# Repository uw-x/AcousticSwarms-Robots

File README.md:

## Hardware
The hardware design for the robots used in the acoustic swarms, including the circuits and PCB files.

## Firmware
This subfolder contains the source code for the firmware we upload on the robots. The firmware is compiled and uploaded using [Segger Embedded Studio v7.22](https://www.segger.com/downloads/embedded-studio/) and the [nRF5 SDK v17.0.1](https://www.nordicsemi.com/Products/Development-software/nRF5-SDK/Download#infotabs). 

## Receiver
This subfolder contains the source code and firmware for the receiver used to transmit data to and from the robot swarm. It also contains the 2D robot localization algorithm.

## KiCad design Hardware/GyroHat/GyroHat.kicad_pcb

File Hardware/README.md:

# Robot Hardware
This subfolder contains information pertaining to the robot design files.

## What's included
This folder contains the following directories:

**CAD**: STL files for the 3D models used. The base station is printed using an Ultimaker 3 with white PLA. The rest of the design files use a Formlabs Form 3 printer with black resin. The robot body takes inspiration from [Zooids](https://github.com/ShapeLab/SwarmUI), with various modifications. However, we use the 3D printed wheels are the same.

**Robot**: BoM & PCB design files for the robot main circuit.

**GyroHat**: BoM & PCB design files for the gyroscope hat on the top of the robot.

**SensorBars**: BoM & PCB design files for the sensor bar used to detect edges.

## How to use
To use these circuit design files, you will need the circuit design software KiCad. Simply import the schematics and PCB layouts into your preferred software and you can begin customizing and optimizing the design to fit your specific needs.

During assembly, we place two wire connecting the metallic balls at the bottom of the robot to the PCB at the top. One ball is connected to the circuit ground while the other is connected through the +5V battery input (the Vin TestPoint in the PCB). For protection, this ball is connected through a [diode](https://www.digikey.com/ordering/shoppingcart?display=yes&itemSeqs=398627123,398628073,398633233&reprice=2).
We use [micro DC motors](https://www.firgelliauto.com/products/mini-motor-micro-motor) from Firgelli Auto.
We use [M2x0.4mm Thread, 6m Long screws](https://www.mcmaster.com/catalog/129/3394/90116A010) and [1/8 inch diameter aluminium balls](https://www.mcmaster.com/catalog/129/4186/34665K29) from McMaster-Carr.
We use [M1.5x8 Buna-N O-Ring](https://www.amazon.com/gp/product/B00595LLJK/ref=ppx_yo_dt_b_asin_title_o05_s00?ie=UTF8&th=1) from Amazon.

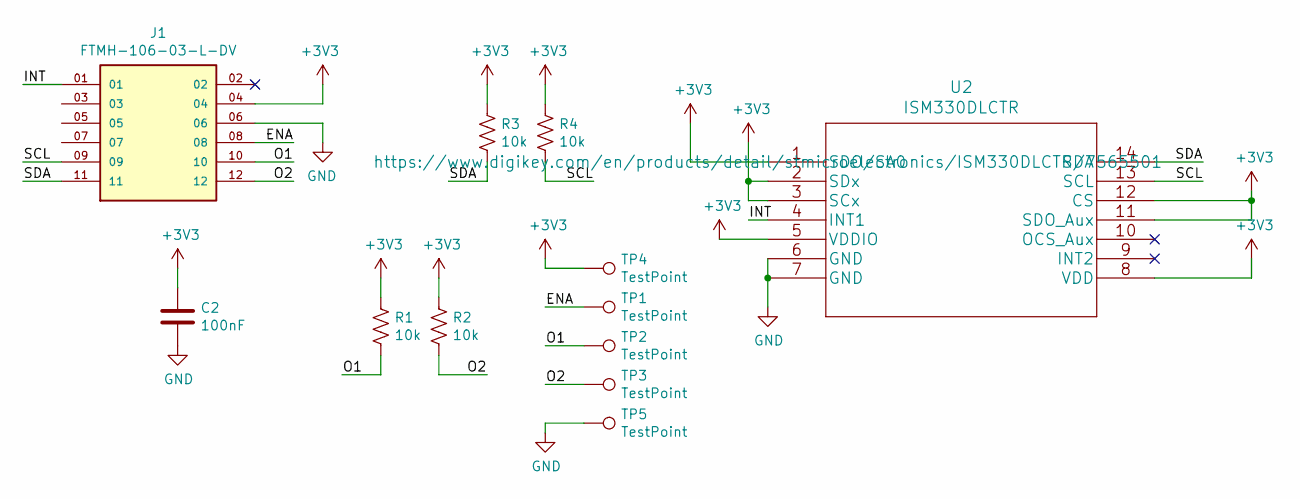
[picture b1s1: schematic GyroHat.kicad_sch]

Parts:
C2: 100nF; C_0402_1005Metric
J1: FTMH-106-03-L-DV; SAMTEC_FTMH-106-03-L-DV
R1, R2, R3, R4: 10k; R_0402_1005Metric
TP1, TP2, TP3, TP4, TP5: TestPoint; Wire Pad
U2: ISM330DLCTR; LGA-14_3x2.5mm_P0.5mm_LayoutBorder3x4y

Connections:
+3V3: C2.1, J1.04, R1.1, R2.1, R3.1, R4.1, TP4.1, U2.1 (SDO/SA0), U2.2 (SDx), U2.3 (SCx), U2.5 (VDDIO), U2.8 (VDD), U2.11 (SDO_Aux), U2.12 (CS)
/ENA: J1.08, TP1.1
/INT: J1.01, U2.4 (INT1)
/O1: J1.10, R1.2, TP2.1
/O2: J1.12, R2.2, TP3.1
/SCL: J1.09, R4.2, U2.13 (SCL)
/SDA: J1.11, R3.2, U2.14 (SDA)
GND: C2.2, J1.06, TP5.1, U2.6 (GND), U2.7 (GND)

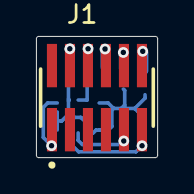
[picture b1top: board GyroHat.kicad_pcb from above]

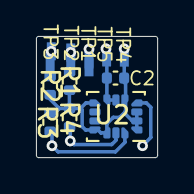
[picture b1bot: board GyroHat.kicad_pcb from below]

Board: 2 copper layers, 6.7 x 6.7 mm, 12 parts (11 on the bottom side), 8 nets.

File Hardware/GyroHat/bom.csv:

Component,Description,References,Value,Footprint,Quantity Per PCB,Datasheet,MANUFACTURER
1,CAP CER 0.1UF 25V X5R 0402,C2,100nF,C_0402_1005Metric,1,https://media.digikey.com/pdf/Data%20Sheets/Samsung%20PDFs/C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,Samsung Electro-Mechanics
2,CONN HEADER SMD 12POS 1MM,J1,FTMH-106-03-L-DV,SAMTEC_FTMH-106-03-L-DV,1,https://www.digikey.com/en/products/detail/samtec-inc/FTMH-1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,SAMTEC
3,RES SMD 10K OHM 5% 1/5W 0402,R1 R2 R3 R4,10k,R_0402_1005Metric,4,https://fscdn.rohm.com/en/products/databook/datasheet/passiv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,Rohm Semiconductor
4,INEMO INERTIAL MODULE,U2,ISM330DLCTR,LGA-14_3x2.5mm_P0.5mm_LayoutBorder3x4y,1,https://www.digikey.com/en/products/detail/stmicroelectronic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,STMicroelectronics
,,,,,,,
,,,,,,,
,,,,,,,
,,,,,,,
,,,,,,,
Component Groups:,4,,,,,,
Component Count:,7,,,,,,
Fitted Components:,7,,,,,,
Number of PCBs:,1,,,,,,
Total components:,7,,,,,,
Schematic Version:,,,,,,,
Schematic Date:,,,,,,,
PCB Variant:,default,,,,,,
BoM Date:,Fri 04 Aug 2023 09:19:59 AM,,,,,,
Schematic Source:,GyroHat.kicad_sch,,,,,,
KiCad Version:,Eeschema 6.0.2+dfsg-1,,,,,,

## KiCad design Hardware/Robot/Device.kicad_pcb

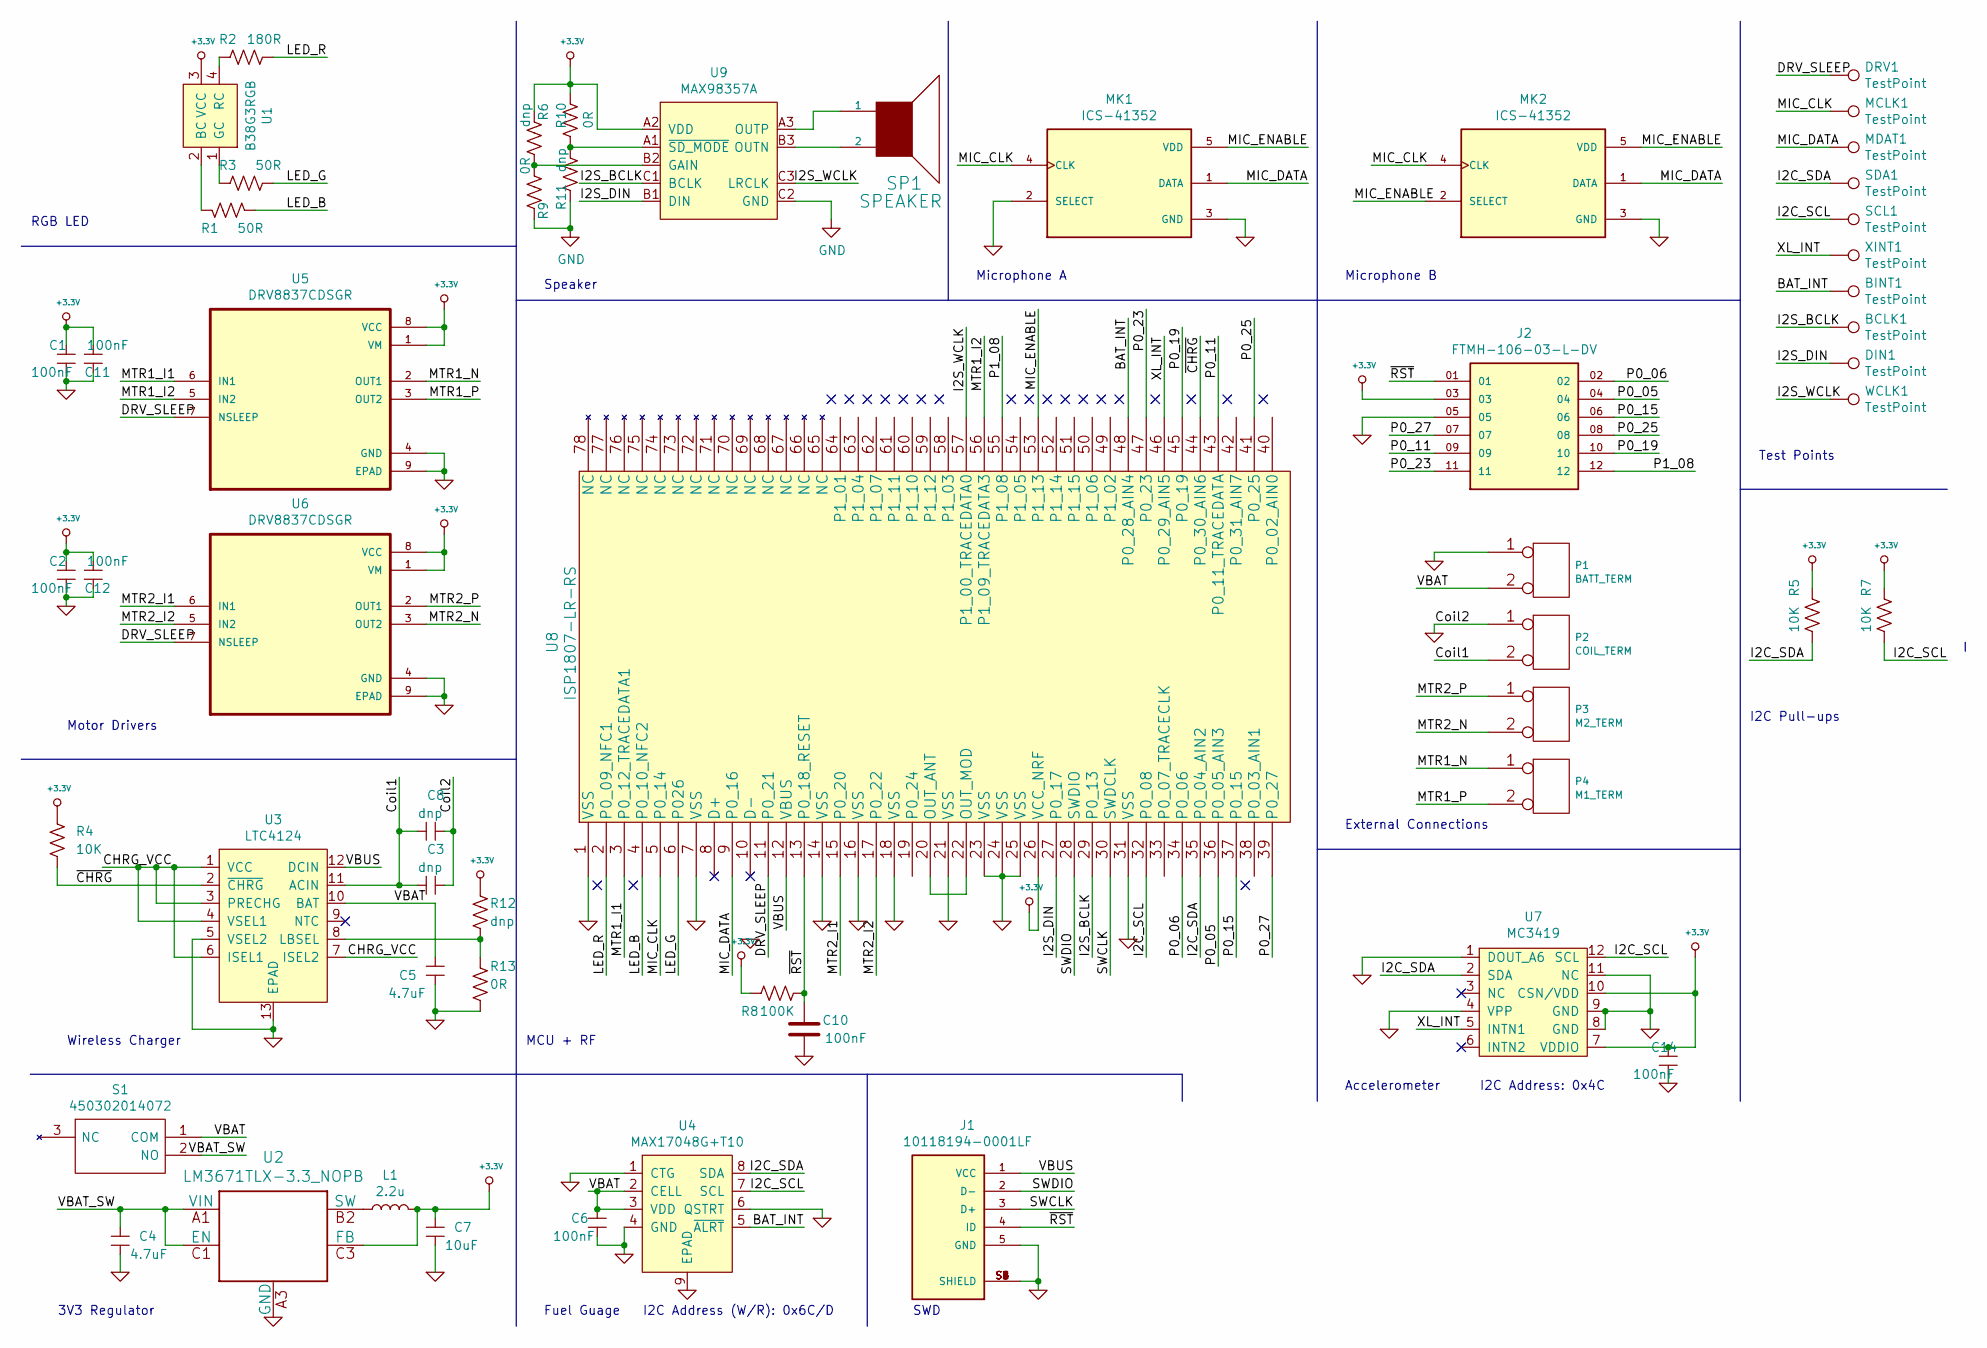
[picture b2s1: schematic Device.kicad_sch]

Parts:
BCLK1: TestPoint; TestPoint_Pad_D1.0mm
BINT1: TestPoint; TestPoint_Pad_D1.0mm
C1, C2, C6, C10, C11, C12, C14: 100nF; C_0402_1005Metric; Manufacturer P/N CL05A104KA5NNNC
C3, C8: dnp; C_0402_1005Metric
C4, C5: 4.7uF; C_0603_1608Metric; Manufacturer P/N CL10A475KQ8NNNC
C7: 10uF; C_0603_1608Metric; Manufacturer P/N 0603YW106MAT2A
DIN1: TestPoint; TestPoint_Pad_D1.0mm
DRV1: TestPoint; TestPoint_Pad_D1.0mm
J1: 10118194-0001LF; AMPHENOL_10118194-0001LF; PARTREV B
J2: FTMH-106-03-L-DV; SAMTEC_FTMH-106-03-L-DV; Manufacturer P/N FTMH-106-03-L-DV
L1: 2.2u; L_0805_2012Metric; Manufacturer P/N DFE201210U-2R2M=P2
MCLK1: TestPoint; TestPoint_Pad_D1.0mm
MDAT1: TestPoint; TestPoint_Pad_D1.0mm
MK1, MK2: ICS-41352; MIC_ICS-41350; Manufacturer P/N ICS-41352
P1: BATT_TERM; JST_ACH_BM02B-ACHSS-GAN-ETF_1x02-1MP_P1.20mm_Vertical; Manufacturer P/N BM02B-ACHSS-GAN-ETF(LF)(SN
P2: COIL_TERM; TestPoint_2Pads_Pitch2.54mm_Drill0.8mm
P3: M2_TERM; PinHeader_1x02_P1.27mm_Vertical
P4: M1_TERM; PinHeader_1x02_P1.27mm_Vertical
R1, R3: 50R; R_0402_1005Metric; Manufacturer P/N AC0402JR-0750RL
R2: 180R; R_0402_1005Metric; Manufacturer P/N CRGCQ0402F180K
R4, R5, R7: 10K; R_0402_1005Metric; Manufacturer P/N ESR01MZPJ103
R6, R11, R12: dnp; R_0402_1005Metric
R8: 100K; R_0402_1005Metric; Manufacturer P/N RT0402BRE07100KL
R9, R10, R13: 0R; R_0402_1005Metric; Manufacturer P/N RMCF0402ZT0R00
S1: 450302014072; Manufacturer P/N 450302014072
SCL1: TestPoint; TestPoint_Pad_D1.0mm
SDA1: TestPoint; TestPoint_Pad_D1.0mm
SP1: SPEAKER; CUI_CMT-4023S-SMT-TR; Manufacturer P/N SMT-0440-T-HT-R
U1: B38G3RGB; B38G3RGB10D0003H2U1930; Manufacturer P/N B38G3RGB-10D0003H2U1930
U2: LM3671TLX-3.3_NOPB; LM3671TLX-3.3&slash_NOPB; Manufacturer P/N LM3671TLX-3.3/NOPB
U3: LTC4124; LTC4124EV-TRMPBF; Manufacturer P/N LTC4124EV#TRMPBF
U4: MAX17048G+T10; SON50P200X200X80-9N; Manufacturer P/N MAX17048G+T10
U5, U6: DRV8837CDSGR; SON50P200X200X80-9N; Manufacturer P/N DRV8837CDSGR
U7: MC3419; LGA-12_2x2mm_P0.5mm; Manufacturer P/N MC3419
U8: ISP1807-LR-RS; Manufacturer P/N ISP1807-LR-RS
U9: MAX98357A; Maxim_WLP-9_1.595x1.415_Layout3x3_P0.4mm_Ball0.27mm_Pad0.25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; Manufacturer P/N MAX98357AEWL+T
WCLK1: TestPoint; TestPoint_Pad_D1.0mm
XINT1: TestPoint; TestPoint_Pad_D1.0mm

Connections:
+3.3V: C1.1, C2.1, C7.2, C11.2, C12.2, C14.1, J2.03, L1.2, R4.1, R5.1, R6.2, R7.1, R8.1, R10.1, R12.1, U1.3 (VCC), U2.C3 (FB), U5.1 (VM), U5.8 (VCC), U6.1 (VM), U6.8 (VCC), U7.7 (VDDIO), U7.10 (CSN/VDD), U8.26 (VCC_NRF), U9.A2 (VDD)
/BAT_INT: BINT1.1, U4.5 (~ALRT), U8.48 (P0_28_AIN4)
/CHRG_VCC: U3.1 (VCC), U3.3 (PRECHG), U3.4 (VSEL1), U3.6 (ISEL1), U3.7 (ISEL2)
/Coil1: C3.2, C8.2, P2.2 (PM), U3.11 (ACIN)
/DRV_SLEEP: DRV1.1, U5.7 (NSLEEP), U6.7 (NSLEEP), U8.11 (P0_21)
/I2C_SCL: R7.2, SCL1.1, U4.7 (SCL), U7.12 (SCL), U8.32 (P0_08)
/I2C_SDA: R5.2, SDA1.1, U4.8 (SDA), U7.2 (SDA), U8.35 (P0_04_AIN2)
/I2S_BCLK: BCLK1.1, U8.29 (P0_13), U9.C1 (BCLK)
/I2S_DIN: DIN1.1, U8.27 (P0_17), U9.B1 (DIN)
/I2S_WCLK: U8.57 (P1_00_TRACEDATA0), U9.C3 (LRCLK), WCLK1.1
/LED_B: R1.2, U8.4 (P0_10_NFC2)
/LED_G: R3.2, U8.6 (P026)
/LED_R: R2.2, U8.2 (P0_09_NFC1)
/MIC_CLK: MCLK1.1, MK1.4 (CLK), MK2.4 (CLK), U8.5 (P0_14)
/MIC_DATA: MDAT1.1, MK1.1 (DATA), MK2.1 (DATA), U8.9 (P0_16)
/MIC_ENABLE: MK1.5 (VDD), MK2.2 (SELECT), MK2.5 (VDD), U8.53 (P1_13)
/MTR1_I1: U5.6 (IN1), U8.3 (P0_12_TRACEDATA1)
/MTR1_I2: U5.5 (IN2), U8.56 (P1_09_TRACEDATA3)
/MTR1_N: P4.1, U5.2 (OUT1)
/MTR1_P: P4.2 (PM), U5.3 (OUT2)
/MTR2_I1: U6.6 (IN1), U8.15 (P0_20)
/MTR2_I2: U6.5 (IN2), U8.17 (P0_22)
/MTR2_N: P3.2 (PM), U6.3 (OUT2)
/MTR2_P: P3.1, U6.2 (OUT1)
/P0_05: J2.04, U8.36 (P0_05_AIN3)
/P0_06: J2.02, U8.34 (P0_06)
/P0_11: J2.09, U8.43 (P0_11_TRACEDATA)
/P0_15: J2.06, U8.37 (P0_15)
/P0_19: J2.10, U8.45 (P0_19)
/P0_23: J2.11, U8.47 (P0_23)
/P0_25: J2.08, U8.41 (P0_25)
/P0_27: J2.07, U8.39 (P0_27)
/P1_08: J2.12, U8.55 (P1_08)
/SWCLK: J1.3 (D+), U8.30 (SWDCLK)
/SWDIO: J1.2 (D-), U8.28 (SWDIO)
/VBAT: C5.1, C6.2, P1.2 (PM), S1.1 (COM), U3.10 (BAT), U4.2 (CELL), U4.3 (VDD)
/VBAT_SW: C4.2, S1.2 (NO), U2.A1 (VIN), U2.C1 (EN)
/VBUS: J1.1 (VCC), U3.12 (DCIN), U8.12 (VBUS)
/XL_INT: U7.5 (INTN1), U8.46 (P0_29_AIN5), XINT1.1
/~CHRG: R4.2, U3.2 (~CHRG), U8.44 (P0_30_AIN6)
/~RST: C10.1, J1.4 (ID), J2.01, R8.2, U8.13 (P0_18_RESET)
GND: C1.2, C2.2, C3.1, C4.1, C5.2, C6.1, C7.1, C8.1, C10.2, C11.1, C12.1, C14.2, J1.5 (GND), J1.S1 (SHIELD), J1.S2 (SHIELD), J1.S3 (SHIELD), J1.S4 (SHIELD), J1.S5 (SHIELD), J1.S6 (SHIELD), J2.05, MK1.2 (SELECT), MK1.3 (GND), MK2.3 (GND), P1.1, P2.1, R9.1, R11.1, R13.2, U2.A3 (GND), U3.5 (VSEL2), U3.13 (EPAD), U4.1 (CTG), U4.4 (GND), U4.6 (QSTRT), U4.9 (EPAD), U5.4 (GND), U5.9 (EPAD), U6.4 (GND), U6.9 (EPAD), U7.1 (DOUT_A6), U7.4 (VPP), U7.8 (GND), U7.9 (GND), U7.11 (NC), U8.1 (VSS), U8.7 (VSS), U8.14 (VSS), U8.16 (VSS), U8.18 (VSS), U8.21 (VSS), U8.23 (VSS), U8.24 (VSS), U8.25 (VSS), U8.31 (VSS), U9.C2 (GND)
unnamed: L1.1, U2.B2 (SW)
unnamed: R1.1, U1.2 (BC)
unnamed: R2.1, U1.4 (RC)
unnamed: R3.1, U1.1 (GC)
unnamed: R6.1, R9.2, U9.B2 (GAIN)
unnamed: R10.2, R11.2, U9.A1 (~SD_MODE)
unnamed: R12.2, R13.1, U3.8 (LBSEL)
unnamed: SP1.1, U9.A3 (OUTP)
unnamed: SP1.2, U9.B3 (OUTN)
unnamed: U8.20 (OUT_ANT), U8.22 (OUT_MOD)

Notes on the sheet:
3V3 Regulator
I2C Pull-ups
Test Points
Wireless Charger
SWD
MCU + RF
RGB LED
Motor Drivers
Speaker
Fuel Guage
Microphone B
External Connections
Accelerometer
Microphone A
I2C Address: 0x4C
I2C Address (W/R): 0x6C/D

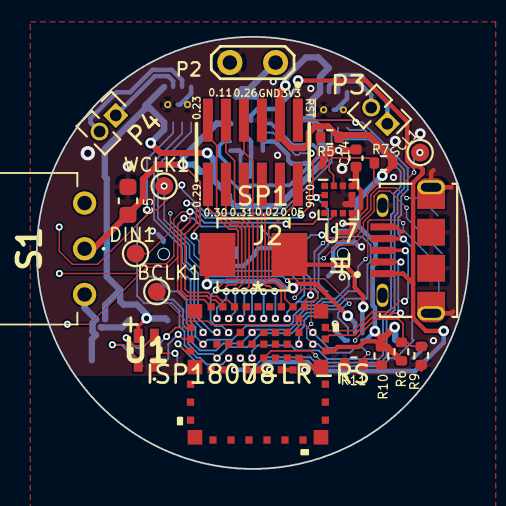
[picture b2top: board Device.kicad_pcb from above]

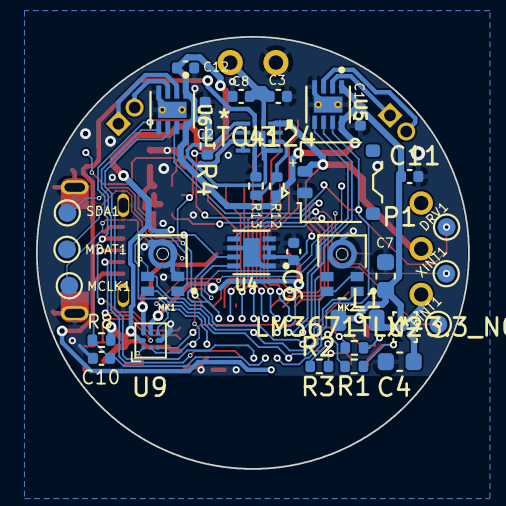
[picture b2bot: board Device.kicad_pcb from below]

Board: 2 copper layers, 24.0 x 24.0 mm, 55 parts (33 on the bottom side), 52 nets.

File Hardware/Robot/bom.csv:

#,References,Value,Datasheet,Description,Manufacturer,Manufacturer P/N,Vendor,Vendor P/N,Quantity,Notes
1,">  C3, C8",dnp,,Do Not Place,,,,,2,
2,">  C4, C5",4.7uF,https://media.digikey.com/pdf/Data%20Sheets/Samsung%20PDFs/C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,CAP CER 4.7UF 10V X5R 0603,Samsung Electro-Mechanics,CL10A475KQ8NNNC,Digi-key,1276-1045-2-ND,2,
3,    C7,10uF,https://datasheets.kyocera-avx.com/x6s-dielectric.pdf,CAP CER 10UF 16V X6S 0603,KYOCERA AVX,0603YW106MAT2A,Digi-key,478-0603YW106MAT2ATR-ND,1,
4,">  C1, C2, C6, C10-C12, C14",100nF,https://media.digikey.com/pdf/Data%20Sheets/Samsung%20PDFs/C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,CAP CER 0.1UF 25V X5R 0402,Samsung Electro-Mechanics,CL05A104KA5NNNC,Digi-key,1276-1043-2-ND,7,
5,    J1,10118194-0001LF,https://cdn.amphenol-icc.com/media/wysiwyg/files/documentati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,"USB - micro B USB 2.0 Receptacle Connector 5 Position Surface Mount, Right Angle; Through Hole",Amphenol ICC (FCI),10118194-0001LF,Digi-key,609-4618-2-ND,1,
6,    J2,FTMH-106-03-L-DV,https://www.mouser.com/datasheet/2/527/ftmh_sm-2854321.pdf,Board to Board & Mezzanine Connectors 1.00 mm Surface Mount Micro Terminal Strip,Samtec,FTMH-106-03-L-DV,Mouser,200-FTMH10603LDV,1,
7,    L1,2.2u,https://search.murata.co.jp/Ceramy/image/img/P02/J(E)TE243A-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,2.2 µH Shielded Wirewound Inductor 1.2 A 228mOhm Max 0805 (2012 Metric) -,Murata Electronics,DFE201210U-2R2M=P2,Digi-key,490-16592-2-ND,1,
8,">  MK1, MK2",ICS-41352,https://invensense.tdk.com/wp-content/uploads/2016/10/DS-000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,Bottom Port PDM Low Power muti-Mode Microphone with high AOP Mode,TDK-InvenSense,ICS-41352,Digi-key,1428-ICS-41352TR-ND,2,
9,    P1,BATT_TERM,https://www.jst-mfg.com/product/pdf/eng/eACH.pdf,"Connector Header Surface Mount, Right Angle 2 position 0.047"" (1.20mm)",JST Sales America Inc.,BM02B-ACHSS-GAN-ETF(LF)(SN,Digi-key,455-3277-2-ND,1,
10,    P3,M2_TERM,,Do Not Place,,,,,1,Solder motor leads here
11,    P4,M1_TERM,,Do Not Place,,,,,1,Solder motor leads here
12,">  R1, R3",50R,https://www.yageo.com/upload/media/product/productsearch/dat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,RES SMD 50 OHM 5% 1/16W 0402,YAGEO,AC0402JR-0750RL,Digi-key,13-AC0402JR-0750RLTR-ND,2,
13,    R2,180R,https://www.te.com/usa-en/product-5-2176337-2.datasheet.pdf,RES 180 OHM 1% 1/16W 0402,TE Connectivity Passive Product,CRGCQ0402F180K,Digi-key,A129654TR-ND,1,
14,">  R4, R5, R7",10K,https://fscdn.rohm.com/en/products/databook/datasheet/passiv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,RES SMD 10K OHM 5% 1/5W 0402,Rohm Semiconductor,ESR01MZPJ103,Digi-key,RHM1003TR-ND,3,
15,">  R6, R11, R12",dnp,,Do Not Place,,,,,3,
16,    R8,100K,https://www.yageo.com/upload/media/product/productsearch/dat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,RES SMD 100K OHM 0.1% 1/16W 0402,YAGEO,RT0402BRE07100KL,Digi-key,YAG2304TR-ND,1,
17,">  R9, R10, R13",0R,https://www.seielect.com/Catalog/SEI-RMCF_RMCP.pdf,RES 0 OHM JUMPER 1/16W 0402,Stackpole Electronics Inc,RMCF0402ZT0R00,Digi-key,RMCF0402ZT0R00TR-ND,3,
18,    S1,450302014072,http://www.farnell.com/datasheets/1913864.pdf,Through Hole Slide Switch SPDT On-On 100 mA@ 42 V dc Slide,Wurth Elektronik,450302014072,Mouser,710-450302014072,1,
19,SP1,SPEAKER,http://puiaudio.com/pdf/AS01008MR-3-LW100-R.pdf,  8 Ohms General Purpose Speaker 500 mW 800 Hz ~ 20 kHz Top Round,"PUI Audio, Inc.",AS01008MR-3-LW100-R,Digi-key,668-AS01008MR-3-LW100-R-ND,1,"Footprint should not match speaker. During fabrication, DO NOT PLACE ANY COMPONENT HERE. Manually solder speaker leads after receiving boards instead."
20,    U1,B38G3RGB,https://media.digikey.com/pdf/Data%20Sheets/Harvatek%20PDFs/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,"Red, Green, Blue (RGB) - LED Indication - Discrete 2V Red, 3V Green, 3V Blue 0606 (1616 Metric)",Harvatek Corporation,B38G3RGB-10D0003H2U1930,Digi-key,3147-B38G3RGB-10D0003H2U1930TR-ND,1,
21,    U2,LM3671TLX-3.3_NOPB,https://www.ti.com/general/docs/suppproductinfo.tsp?distId=1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,"Buck Switching Regulator IC Positive Fixed 3.3V 1 Output 600mA 5-WFBGA, DSBGA",Texas Instruments,LM3671TLX-3.3/NOPB,Digi-key,LM3671TLX-3.3/NOPBTR-ND,1,
22,    U3,LTC4124,https://www.analog.com/media/en/technical-documentation/data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,Wireless Charging ICs 100mA Wireless Li-Ion Charger,Analog Devices,LTC4124EV#TRMPBF,Mouser,584-LTC4124EV#TRMPBF,1,
23,    U4,MAX17048G+T10,https://datasheets.maximintegrated.com/en/ds/MAX17048-MAX17049.pdf,IC BATT MON LI-ION 1CELL 8TDFN,Analog Devices Inc./Maxim Integrated,MAX17048G+T10,Digi-key,MAX17048G+T10TR-ND,1,
24,">  U5, U6",DRV8837CDSGR,https://www.ti.com/general/docs/suppproductinfo.tsp?distId=1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,IC HALF-BRIDGE DRVR PWM 8WSON,Texas Instruments,DRV8837CDSGR,Digi-key,296-47205-2-ND,2,
25,    U7,MC3419,https://www.mouser.com/datasheet/2/821/MEMSIC_MC3419_Datashe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,Accelerometers Small Digital 3-axis Accelerometer Sensor,MEMSIC,MC3419,Mouser,498-MC3419,1,
26,    U8,ISP1807-LR-RS,https://www.insightsip.com/fichiers_insightsip/pdf/ble/ISP18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,"Bluetooth Bluetooth v5.0, Thread, Zigbee® Transceiver Module 2.402GHz ~ 2.48GHz Integrated, Trace Surface Mount",Insight SIP,ISP1807-LR-RS,Digi-key,1786-1019-2-ND,1,
27,    U9,MAX98357A,https://datasheets.maximintegrated.com/en/ds/MAX98357A-MAX98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,IC AMP CLASS D MONO 3.2W 9WLP,Analog Devices Inc./Maxim Integrated,MAX98357AEWL+T,Digi-key,MAX98357AEWL+TTR-ND,1,

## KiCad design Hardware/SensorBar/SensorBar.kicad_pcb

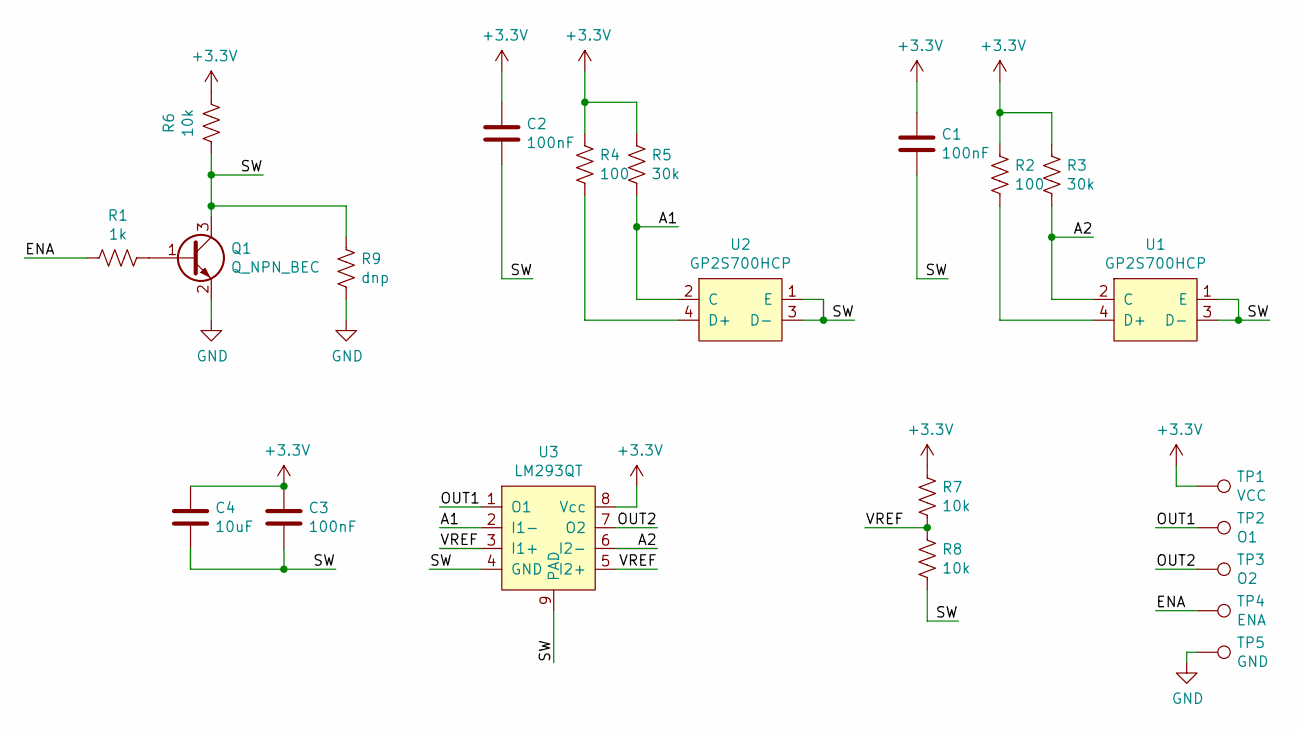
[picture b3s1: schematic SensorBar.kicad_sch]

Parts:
C1, C2, C3: 100nF; C_0402_1005Metric
C4: 10uF; C_0402_1005Metric
Q1: Q_NPN_BEC; SOT-23
R1: 1k; R_0402_1005Metric
R2, R4: 100; R_0402_1005Metric
R3, R5: 30k; R_0402_1005Metric
R6, R7, R8: 10k; R_0402_1005Metric
R9: dnp; R_0402_1005Metric
TP1: VCC; TestPoint_Pad_D1.0mm
TP2: O1; TestPoint_Pad_D1.0mm
TP3: O2; TestPoint_Pad_D1.0mm
TP4: ENA; TestPoint_Pad_D1.0mm
TP5: GND; TestPoint_Pad_D1.0mm
U1, U2: GP2S700HCP
U3: LM293QT; DFN-8-1EP_2x2mm_P0.5mm_EP0.6x1.2mm

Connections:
+3V3: C1.1, C2.1, C3.1, C4.1, R2.2, R3.2, R4.2, R5.2, R6.1, R7.2, TP1.1, U3.8 (Vcc)
/A1: R5.1, U2.2 (C), U3.2 (I1-)
/A2: R3.1, U1.2 (C), U3.6 (I2-)
/ENA: R1.2, TP4.1
/OUT1: TP2.1, U3.1 (O1)
/OUT2: TP3.1, U3.7 (O2)
/SW: C1.2, C2.2, C3.2, C4.2, Q1.3 (C), R6.2, R8.1, R9.2, U1.1 (E), U1.3 (D-), U2.1 (E), U2.3 (D-), U3.4 (GND), U3.9 (PAD)
/VREF: R7.1, R8.2, U3.3 (I1+), U3.5 (I2+)
GND: Q1.2 (E), R9.1, TP5.1
unnamed: Q1.1 (B), R1.1
unnamed: R2.1, U1.4 (D+)
unnamed: R4.1, U2.4 (D+)

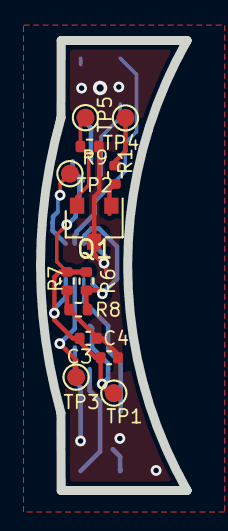
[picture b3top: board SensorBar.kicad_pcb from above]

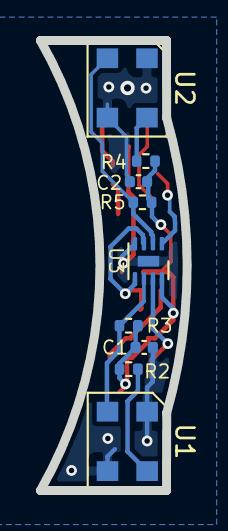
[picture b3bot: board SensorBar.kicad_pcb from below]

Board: 2 copper layers, 8.1 x 25.0 mm, 22 parts (9 on the bottom side), 12 nets.

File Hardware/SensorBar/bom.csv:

Component,Description,References,Value,Footprint,Quantity Per PCB,Datasheet
1,CAP CER 0.1UF 25V X5R 0402,C1 C2 C3,100nF,C_0402_1005Metric,3,https://media.digikey.com/pdf/Data%20Sheets/Samsung%20PDFs/C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
2,CAP CER 10UF 16V X6S 0603,C4,10uF,C_0402_1005Metric,1,https://datasheets.kyocera-avx.com/x6s-dielectric.pdf
3,TRANS NPN 45V 0.5A TO236AB,Q1,Q_NPN_BEC,SOT-23,1,https://www.digikey.com/en/products/detail/nexperia-usa-inc/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
4,RES 100 OHM 1% 1/16W 0402,R2 R4,100,R_0402_1005Metric,2,https://www.vishay.com/docs/28705/mcx0x0xpro.pdf
5,RES 1K OHM 1% 1/16W 0402,R1,1k,R_0402_1005Metric,1,https://www.yageo.com/upload/media/product/productsearch/dat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
6,RES SMD 10K OHM 5% 1/5W 0402,R6 R7 R8,10k,R_0402_1005Metric,3,https://fscdn.rohm.com/en/products/databook/datasheet/passiv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
7,RES 30K OHM 1% 1/16W 0402,R3 R5,30k,R_0402_1005Metric,2,https://www.digikey.com/en/products/detail/yageo/RC0402FR-07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
8,PHOTOINTERRUPTER REFLEC 3MM SMD,U1 U2,GP2S700HCP,GP2S700HCP,2,https://global.sharp/products/device/lineup/data/pdf/datashe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
9,IC COMPARATOR 2 GEN PUR 8UFSON,U3,LM293QT,DFN-8-1EP_2x2mm_P0.5mm_EP0.6x1.2mm,1,https://www.st.com/content/ccc/resource/technical/document/d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
,,,,,,
,,,,,,
,,,,,,
,,,,,,
,,,,,,
Component Groups:,10,,,,,
Component Count:,17,,,,,
Fitted Components:,16,,,,,
Number of PCBs:,1,,,,,
Total components:,16,,,,,
Schematic Version:,,,,,,
Schematic Date:,,,,,,
PCB Variant:,default,,,,,
BoM Date:,Fri 04 Aug 2023 09:10:59 AM,,,,,
Schematic Source:,SensorBar.kicad_sch,,,,,
KiCad Version:,Eeschema 6.0.2+dfsg-1,,,,,

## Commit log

2023-08-30 Removed pycache

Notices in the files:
parts and their libraries:
Copyright 2021 Accelerated Designs. All rights reserved.
